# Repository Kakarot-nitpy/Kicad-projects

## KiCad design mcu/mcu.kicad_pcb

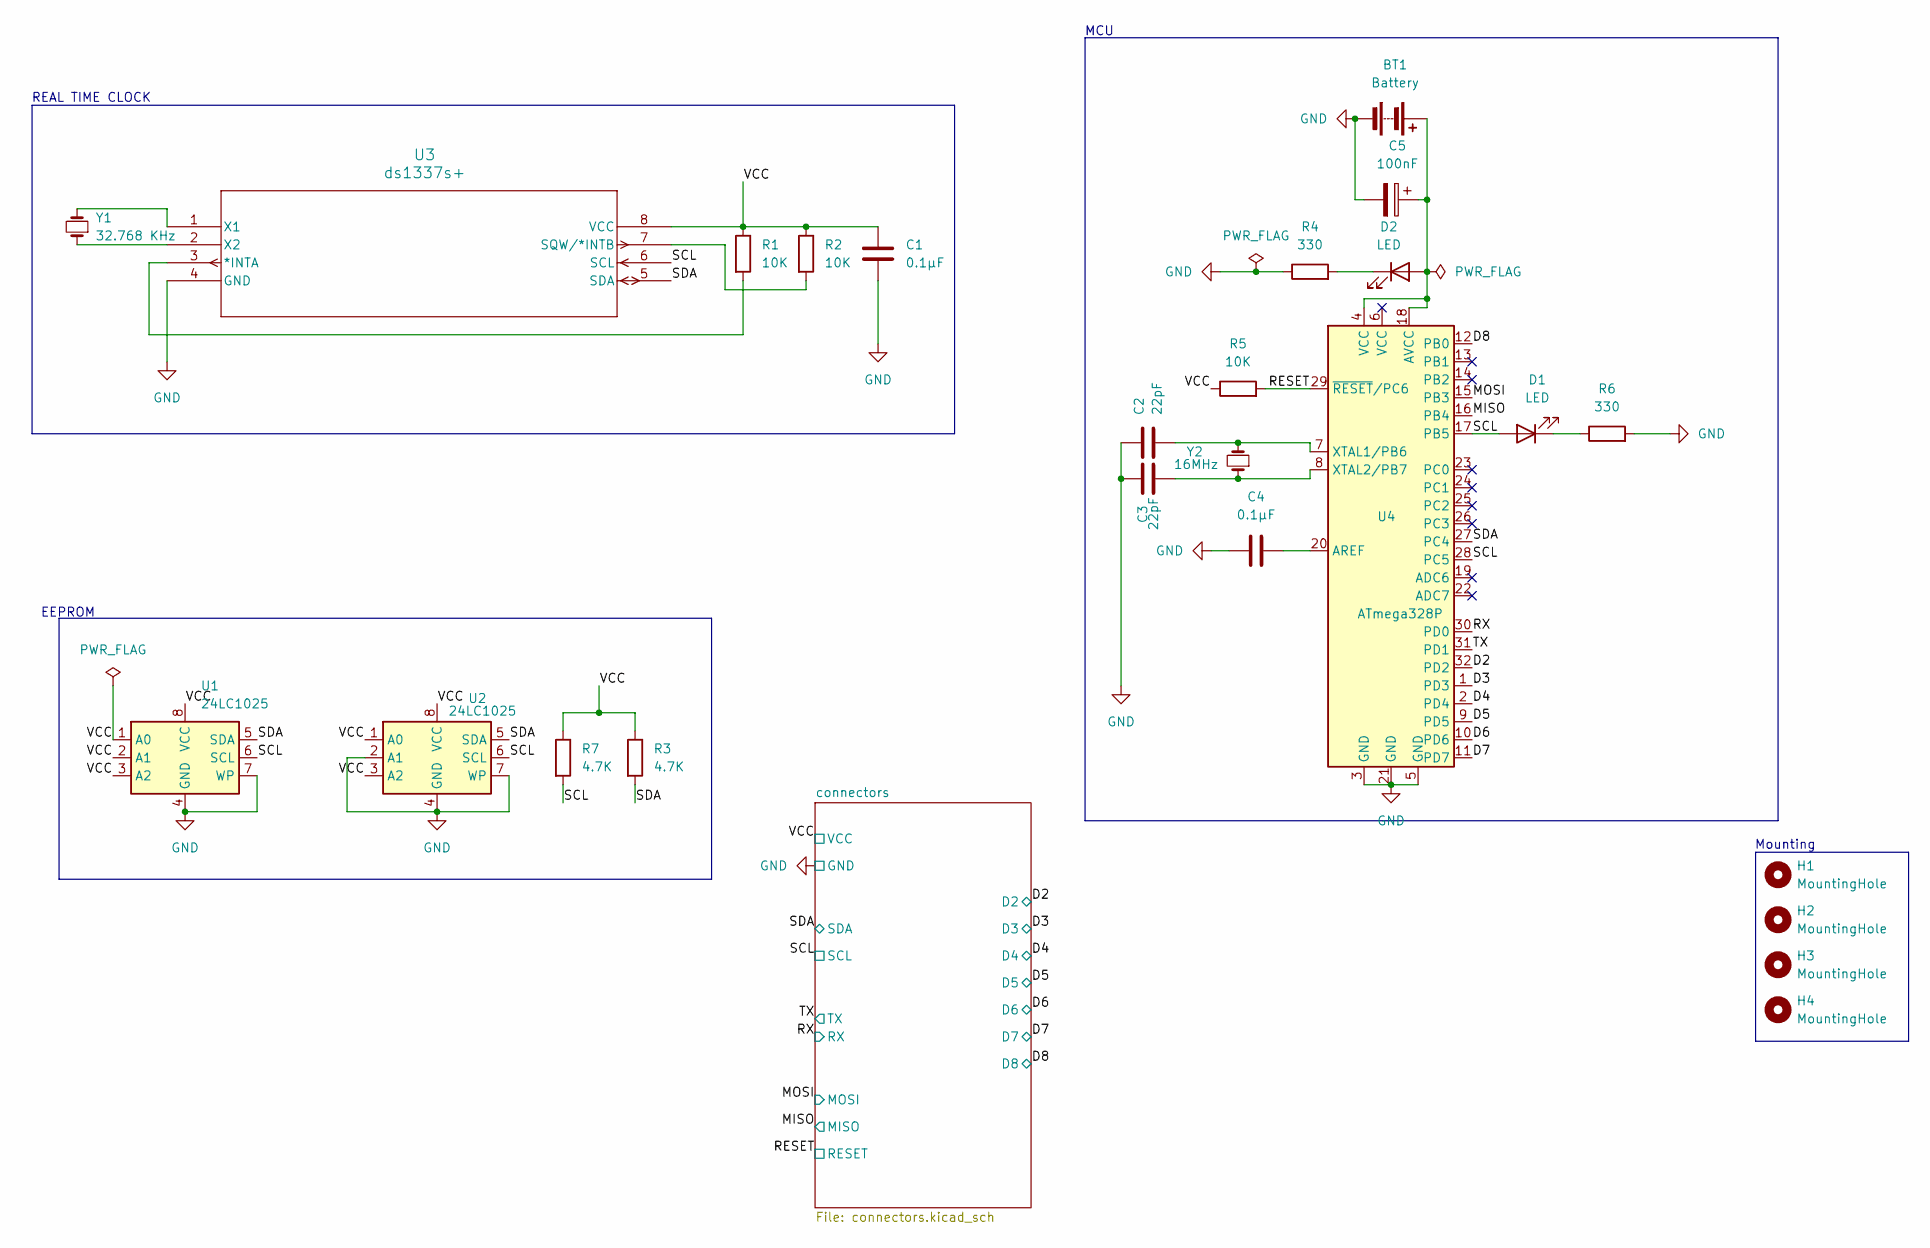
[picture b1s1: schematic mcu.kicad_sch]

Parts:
BT1: Battery; PinHeader_1x02_P2.54mm_Vertical
C1, C4: 0.1µF; C_0805_2012Metric
C2, C3: 22pF; C_0805_2012Metric
C5: 100nF; C_0805_2012Metric
D1, D2: LED; LED_0805_2012Metric
H1, H2, H3, H4: MountingHole; MountingHole_2.1mm
R1, R2, R5: 10K; R_0805_2012Metric
R3, R7: 4.7K; R_0805_2012Metric
R4, R6: 330; R_0805_2012Metric
U1, U2: 24LC1025; SOIC-8_5.3x5.3mm_P1.27mm
U3: ds1337s+; 21-0041B_8_MXM
U4: ATmega328P; QFP80P900X900X120-32N
Y1: 32.768 KHz; Crystal_SMD_5032-2Pin_5.0x3.2mm_HandSoldering
Y2: 16MHz; Crystal_SMD_5032-2Pin_5.0x3.2mm_HandSoldering

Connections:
/D2: U4.32 (PD2); also elsewhere on the board
/D3: U4.1 (PD3); also elsewhere on the board
/D4: U4.2 (PD4); also elsewhere on the board
/D5: U4.9 (PD5); also elsewhere on the board
/D6: U4.10 (PD6); also elsewhere on the board
/D7: U4.11 (PD7); also elsewhere on the board
/D8: U4.12 (PB0); also elsewhere on the board
/MISO: U4.16 (PB4); also elsewhere on the board
/MOSI: U4.15 (PB3); also elsewhere on the board
/RESET: R5.2, U4.29 (~RESET/PC6); also elsewhere on the board
/RX: U4.30 (PD0); also elsewhere on the board
/SCL: D1.2 (A), R7.2, U1.6 (SCL), U2.6 (SCL), U3.6 (SCL), U4.17 (PB5), U4.28 (PC5); also elsewhere on the board
/SDA: R3.2, U1.5 (SDA), U2.5 (SDA), U3.5 (SDA), U4.27 (PC4); also elsewhere on the board
/TX: U4.31 (PD1); also elsewhere on the board
/VCC: C1.1, R1.1, R2.1, R3.1, R5.1, R7.1, U1.1 (A0), U1.2 (A1), U1.3 (A2), U1.8 (VCC), U2.1 (A0), U2.3 (A2), U2.8 (VCC), U3.8 (VCC); also elsewhere on the board
GND: BT1.2 (-), C1.2, C2.1, C3.1, C4.1, C5.2, R4.1, R6.2, U1.4 (GND), U1.7 (WP), U2.2 (A1), U2.4 (GND), U2.7 (WP), U3.4 (GND), U4.3 (GND), U4.5 (GND), U4.21 (GND); also elsewhere on the board
unnamed: BT1.1 (+), C5.1, D2.2 (A), U4.4 (VCC), U4.18 (AVCC)
unnamed: D1.1 (K), R6.1
unnamed: D2.1 (K), R4.2
unnamed: R1.2, U3.3 (*INTA)
unnamed: R2.2, U3.7 (SQW/*INTB)
unnamed: U3.1 (X1), Y1.2
unnamed: U3.2 (X2), Y1.1
unnamed: C4.2, U4.20 (AREF)
unnamed: C2.2, U4.7 (XTAL1/PB6), Y2.2
unnamed: C3.2, U4.8 (XTAL2/PB7), Y2.1

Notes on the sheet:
REAL TIME CLOCK
Mounting
MCU
EEPROM

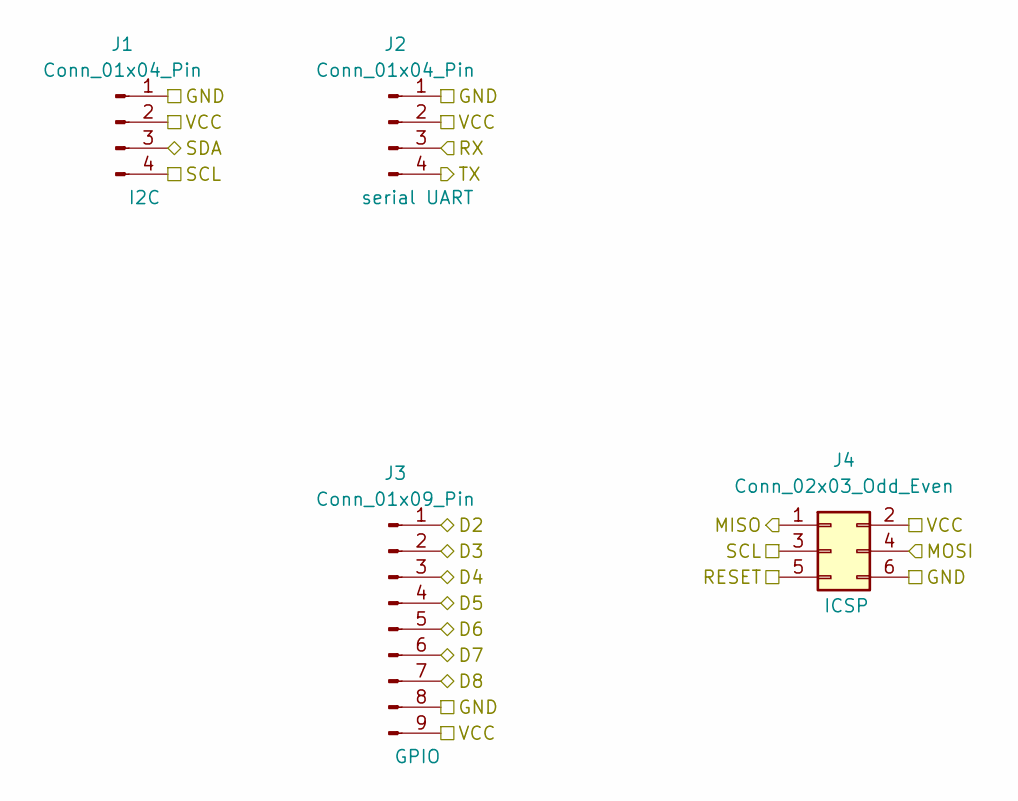
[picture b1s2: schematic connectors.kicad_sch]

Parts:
J1, J2: Conn_01x04_Pin; PinHeader_1x04_P2.54mm_Vertical
J3: Conn_01x09_Pin; PinHeader_1x09_P2.54mm_Vertical
J4: Conn_02x03_Odd_Even; PinHeader_2x03_P2.54mm_Vertical

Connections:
/D2: J3.1; also elsewhere on the board
/D3: J3.2; also elsewhere on the board
/D4: J3.3; also elsewhere on the board
/D5: J3.4; also elsewhere on the board
/D6: J3.5; also elsewhere on the board
/D7: J3.6; also elsewhere on the board
/D8: J3.7; also elsewhere on the board
/MISO: J4.1; also elsewhere on the board
/MOSI: J4.4; also elsewhere on the board
/RESET: J4.5; also elsewhere on the board
/RX: J2.3; also elsewhere on the board
/SCL: J1.4, J4.3; also elsewhere on the board
/SDA: J1.3; also elsewhere on the board
/TX: J2.4; also elsewhere on the board
/VCC: J1.2, J2.2, J3.9, J4.2; also elsewhere on the board
GND: J1.1, J2.1, J3.8, J4.6; also elsewhere on the board

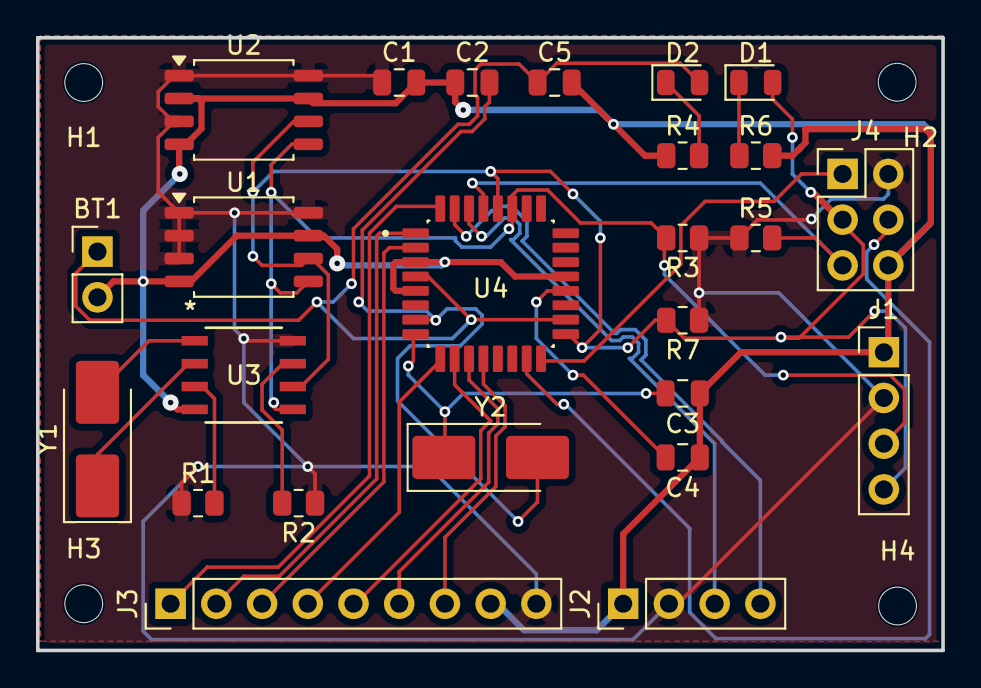
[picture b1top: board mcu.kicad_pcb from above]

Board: 2 copper layers, 50.3 x 34.0 mm, 29 parts (0 on the bottom side), 26 nets.

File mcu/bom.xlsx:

ID | Designator | Footprint | Qty | Designation
1 | BT1 | PinHeader_1x02_P2.54mm_Vertical | 1 | Battery
2 | C1, C4 | C_0805_2012Metric | 2 | 0.1µF
3 | C2, C3 | C_0805_2012Metric | 2 | 22pF
4 | C5 | C_0805_2012Metric | 1 | 100nF
5 | D1, D2 | LED_0805_2012Metric | 2 | LED
6 | J1, J2 | PinHeader_1x04_P2.54mm_Vertical | 2 | Conn_01x04_Pin
7 | J3 | PinHeader_1x09_P2.54mm_Vertical | 1 | Conn_01x09_Pin
8 | J4 | PinHeader_2x03_P2.54mm_Vertical | 1 | Conn_02x03_Odd_Even
9 | R1, R2, R5 | R_0805_2012Metric | 3 | 10K
10 | R3, R7 | R_0805_2012Metric | 2 | 4.7K
11 | R4, R6 | R_0805_2012Metric | 2 | 330Ω
12 | U1, U2 | SOIC-8_5.3x5.3mm_P1.27mm | 2 | 24LC1025
13 | U3 | 21-0041B_8_MXM | 1 | ds1337s+
14 | U4 | QFP80P900X900X120-32N | 1 | ATmega328P
15 | Y1 | Crystal_SMD_5032-2Pin_5.0x3.2mm_HandSoldering | 1 | 32.768 KHz
16 | Y2 | Crystal_SMD_5032-2Pin_5.0x3.2mm_HandSoldering | 1 | 16MHz

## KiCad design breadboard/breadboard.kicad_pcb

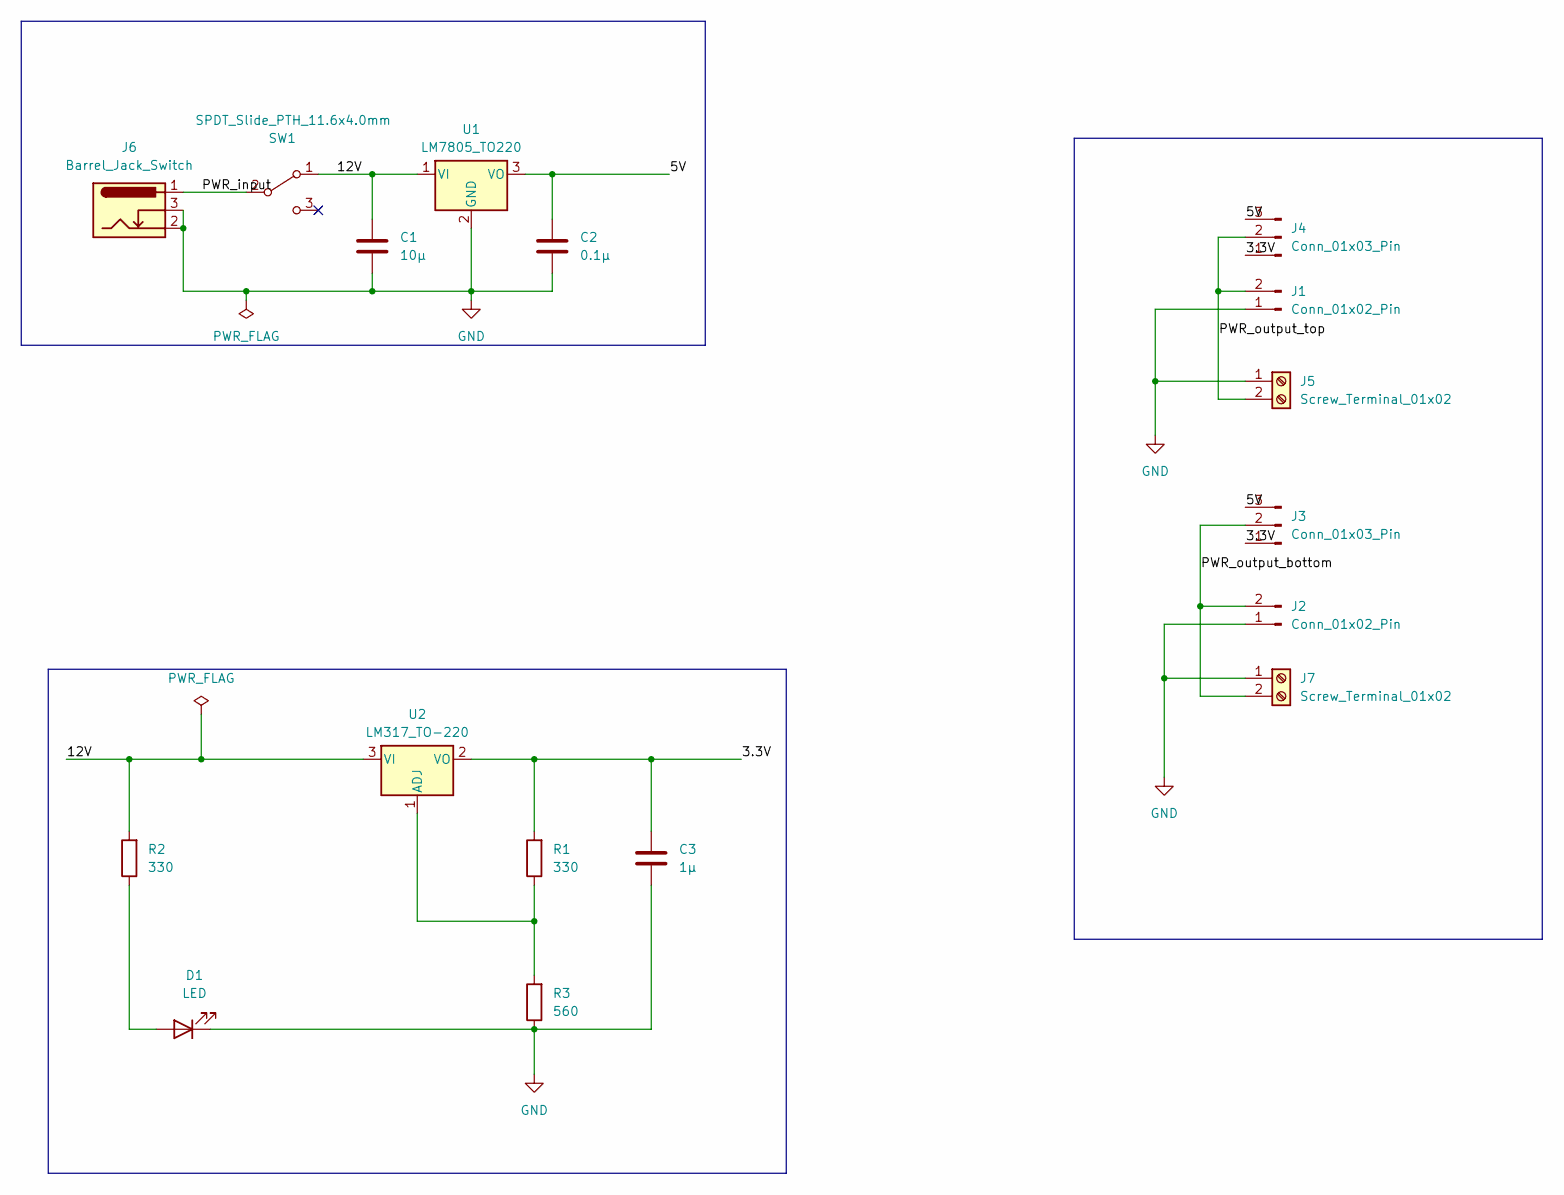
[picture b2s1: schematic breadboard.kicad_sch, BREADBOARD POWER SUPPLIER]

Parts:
C1: 10µ; C_Disc_D3.0mm_W1.6mm_P2.50mm
C2: 0.1µ; C_Disc_D3.0mm_W1.6mm_P2.50mm
C3: 1µ; C_Disc_D3.0mm_W1.6mm_P2.50mm
D1: LED; LED_D5.0mm
J1, J2: Conn_01x02_Pin; PinSocket_1x02_P2.54mm_Vertical
J3, J4: Conn_01x03_Pin; PinSocket_1x03_P2.54mm_Vertical
J5, J7: Screw_Terminal_01x02; TerminalBlock_MaiXu_MX126-5.0-02P_1x02_P5.00mm
J6: Barrel_Jack_Switch; BarrelJack_Horizontal
R1, R2: 330; R_Axial_DIN0204_L3.6mm_D1.6mm_P7.62mm_Horizontal
R3: 560; R_Axial_DIN0204_L3.6mm_D1.6mm_P7.62mm_Horizontal
SW1: SPDT_Slide_PTH_11.6x4.0mm; Slide_SPDT_PTH_11.6x4.0mm
U1: LM7805_TO220; TO-220-3_Vertical
U2: LM317_TO-220; TO-220-3_Vertical

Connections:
/3.3V: C3.1, J3.1, J4.1, R1.2, U2.2 (VO)
/5V: C2.1, J3.3, J4.3, U1.3 (VO)
/12V: C1.1, R2.2, SW1.1 (A), U1.1 (VI), U2.3 (VI)
/PWR_input: J6.1, SW1.2 (B)
/PWR_output_bottom: J2.2, J3.2, J7.2
/PWR_output_top: J1.2, J4.2, J5.2
GND: C1.2, C2.2, C3.2, D1.1 (K), J1.1, J2.1, J5.1, J6.2, J6.3, J7.1, R3.1, U1.2 (GND)
unnamed: D1.2 (A), R2.1
unnamed: R1.1, R3.2, U2.1 (ADJ)

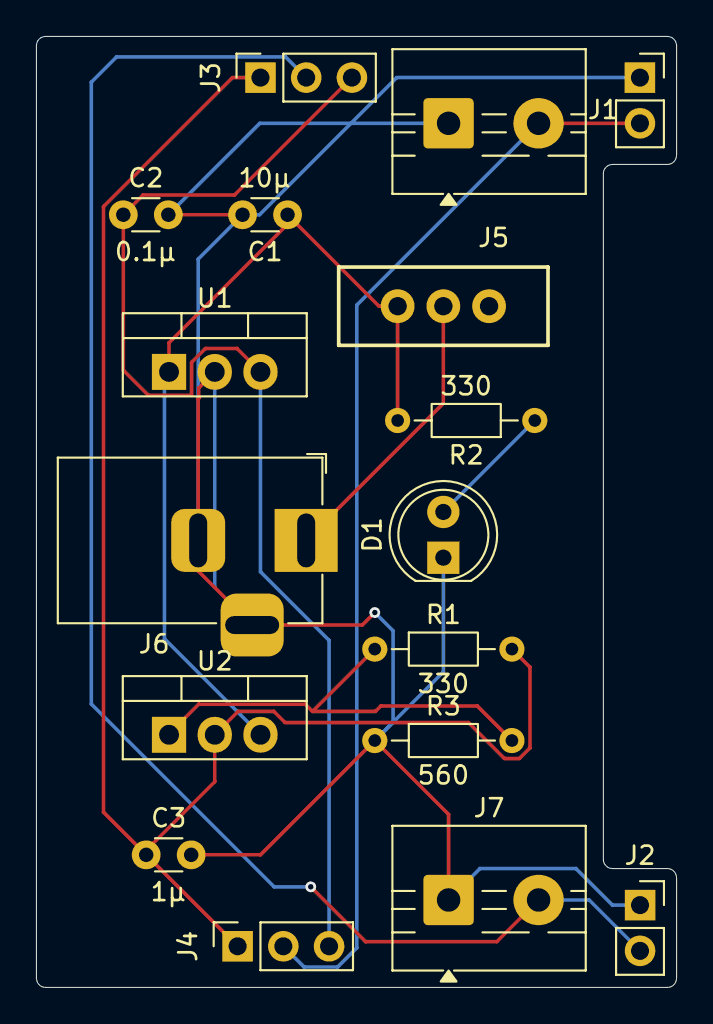
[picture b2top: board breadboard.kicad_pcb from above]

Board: 2 copper layers, 35.6 x 52.8 mm, 17 parts (0 on the bottom side), 9 nets.

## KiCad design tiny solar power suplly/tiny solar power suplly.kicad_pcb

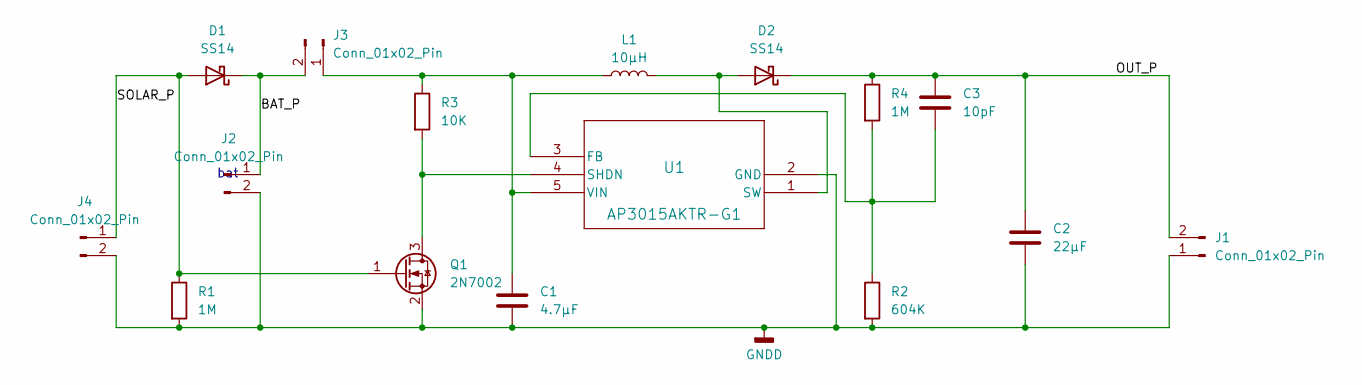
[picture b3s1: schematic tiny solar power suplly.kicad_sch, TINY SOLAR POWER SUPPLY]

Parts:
C1: 4.7µF; C_0805_2012Metric
C2: 22µF; C_1206_3216Metric
C3: 10pF; C_0805_2012Metric
D1, D2: SS14; D_SMA
J1, J2, J4: Conn_01x02_Pin; PinHeader_1x02_P2.54mm_Horizontal
J3: Conn_01x02_Pin; SW_DIP_SPSTx01_Slide_6.7x4.1mm_W6.73mm_P2.54mm_LowProfile_J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
L1: 10µH; L_0805_2012Metric_Pad1.05x1.20mm_HandSolder
Q1: 2N7002; SOT-23
R1, R4: 1M; R_0805_2012Metric
R2: 604K; R_0805_2012Metric
R3: 10K; R_0805_2012Metric
U1: AP3015AKTR-G1; SOT23-5_1P55X2P9_DIO

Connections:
/BAT_P: D1.1 (K), J2.1, J3.2
/OUT_P: C2.1, C3.1, D2.1 (K), J1.2, R4.1
/SOLAR_P: D1.2 (A), J4.1, Q1.1 (G), R1.1
GNDD: C1.2, C2.2, J1.1, J2.2, J4.2, Q1.2 (S), R1.2, R2.2, U1.2 (GND)
unnamed: D2.2 (A), L1.2, U1.1 (SW)
unnamed: C1.1, J3.1, L1.1, R3.1, U1.5 (VIN)
unnamed: Q1.3 (D), R3.2, U1.4 (SHDN)
unnamed: C3.2, R2.1, R4.2, U1.3 (FB)

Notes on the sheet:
bat

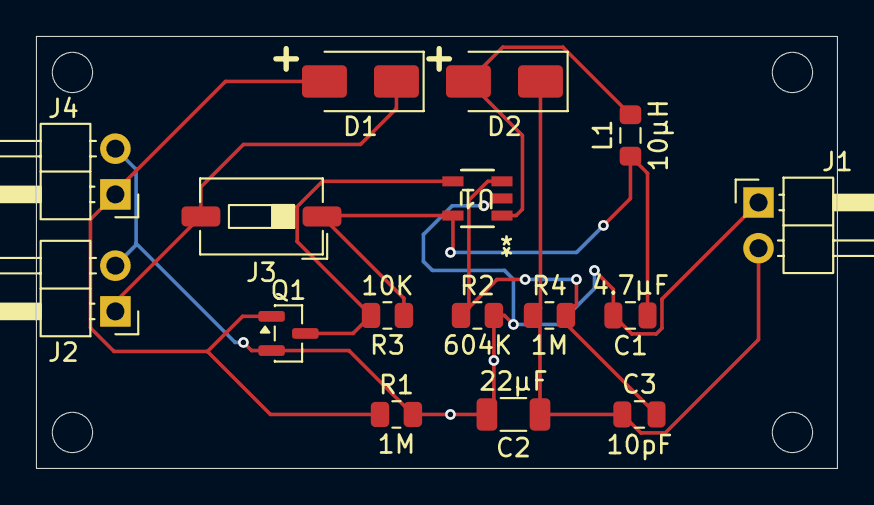
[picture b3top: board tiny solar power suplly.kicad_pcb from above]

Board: 2 copper layers, 44.5 x 24.0 mm, 16 parts (0 on the bottom side), 8 nets.

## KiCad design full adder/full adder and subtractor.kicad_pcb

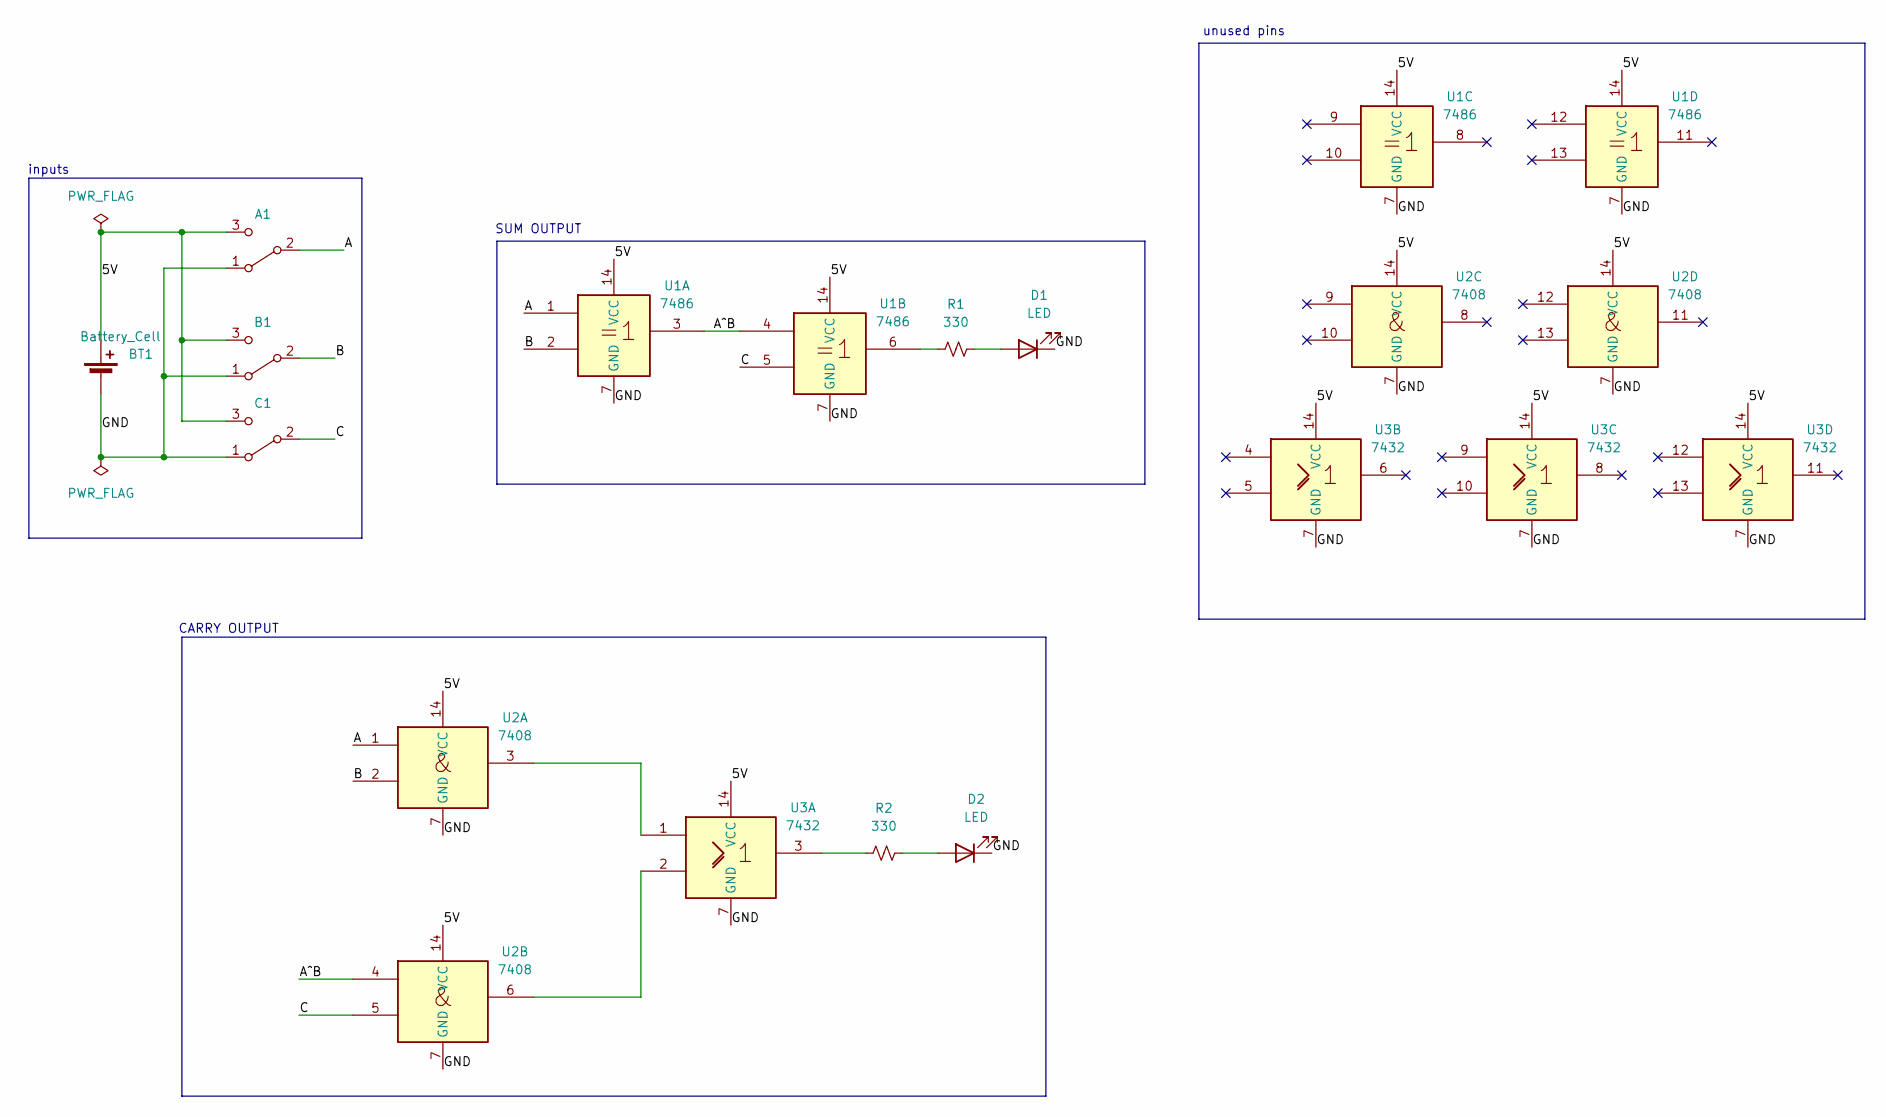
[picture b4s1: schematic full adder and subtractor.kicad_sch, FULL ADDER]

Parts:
A1: SPDT_Slide_PTH_11.6x4.0mm; Slide_SPDT_PTH_11.6x4.0mm
B1: SPDT_Slide_PTH_11.6x4.0mm; Slide_SPDT_PTH_11.6x4.0mm
BT1: Battery_Cell; BatteryHolder_Keystone_1058_1x2032
C1: SPDT_Slide_PTH_11.6x4.0mm; Slide_SPDT_PTH_11.6x4.0mm
D1, D2: LED; LED_D3.0mm
R1, R2: 330; R_0603_1608Metric
U1: 7486; Bosch_LGA-14_3x2.5mm_P0.5mm
U2: 7408; Bosch_LGA-14_3x2.5mm_P0.5mm
U3: 7432; Bosch_LGA-14_3x2.5mm_P0.5mm

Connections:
/5V: A1.3 (C), B1.3 (C), BT1.1 (+), C1.3 (C), U1.14 (VCC), U2.14 (VCC), U3.14 (VCC)
/A: A1.2 (B), U1.1, U2.1
/A^B: U1.3, U1.4, U2.4
/B: B1.2 (B), U1.2, U2.2
/C: C1.2 (B), U1.5, U2.5
/GND: A1.1 (A), B1.1 (A), BT1.2 (-), C1.1 (A), D1.1 (K), D2.1 (K), U1.7 (GND), U2.7 (GND), U3.7 (GND)
unnamed: D1.2 (A), R1.2
unnamed: D2.2 (A), R2.2
unnamed: R1.1, U1.6
unnamed: R2.1, U3.3
unnamed: U2.3, U3.1
unnamed: U2.6, U3.2

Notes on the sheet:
CARRY OUTPUT
inputs
unused pins
SUM OUTPUT

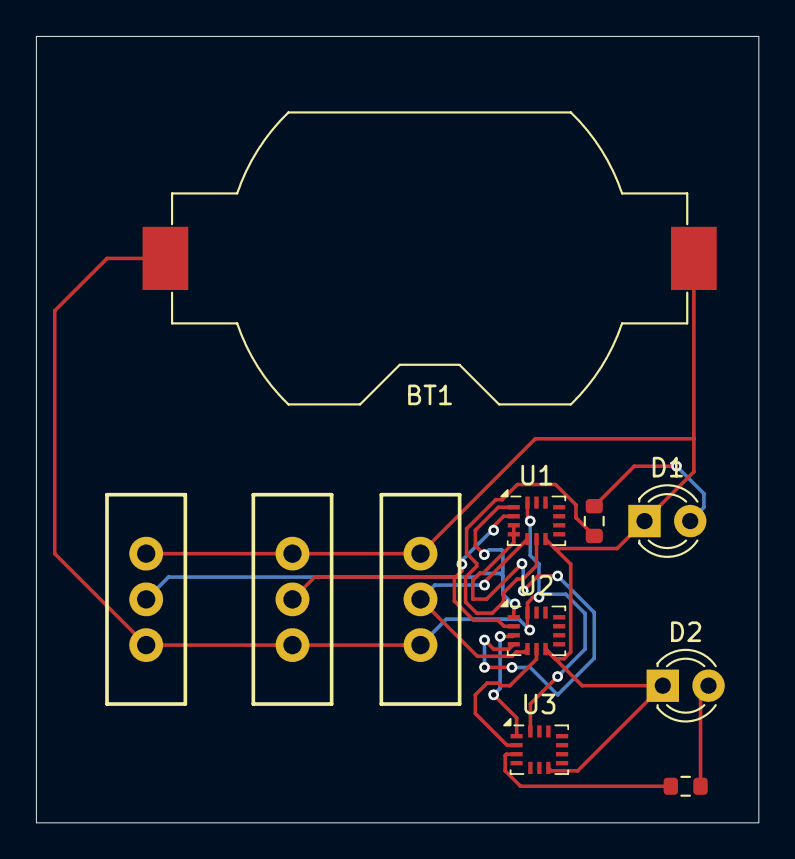
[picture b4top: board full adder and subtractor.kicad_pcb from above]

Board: 2 copper layers, 40.1 x 43.7 mm, 11 parts (0 on the bottom side), 12 nets.

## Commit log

2026-06-06 Create a
